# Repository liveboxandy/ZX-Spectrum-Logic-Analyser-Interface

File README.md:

# ZX-Spectrum-Logic-Analyser-Interface
Copied and Modified from an original idea (V3.1) by HappyLittleDiodes(Jim)

Increased space between Logic Analyser Connectors so as to allow for Pico on 10mm headers on Logic Analyser PCB's

PCB size increased to allow for the above

Added 3 pin header to allow for manual connection to the unused channels (6,7 and 26)

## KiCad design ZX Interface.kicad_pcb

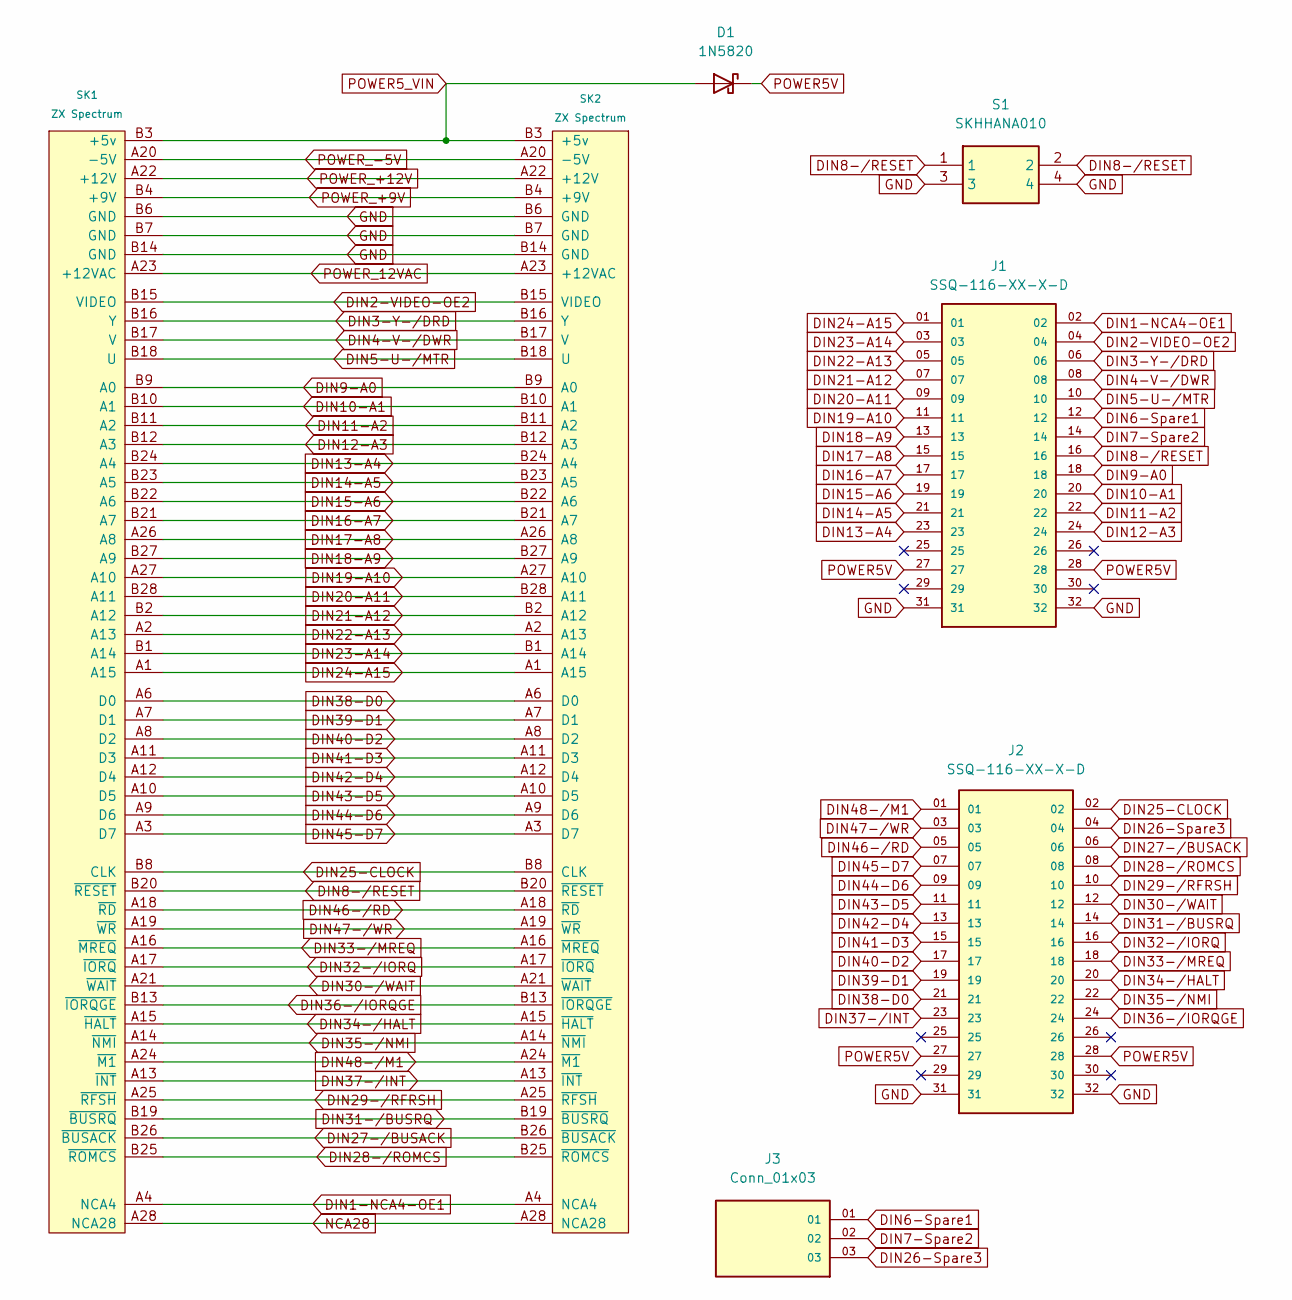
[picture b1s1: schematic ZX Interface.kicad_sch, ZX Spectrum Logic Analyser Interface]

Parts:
D1: 1N5820; D_DO-201AD_P15.24mm_Horizontal
J1, J2: SSQ-116-XX-X-D; SAMTEC_SSQ-116-XX-X-D; PARTREV A
J3: Conn_01x03; SAMTEC_TSW-103-07-G-S; PARTREV R
S1: SKHHANA010; Mouser Part Number 688-SKHHAN
SK1, SK2: ZX Spectrum; ZX_Spectrum_BUS_Edge_Connector Horizontal

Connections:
DIN1-NCA4-OE1: J1.02, SK1.A4 (NCA4), SK2.A4 (NCA4)
DIN2-VIDEO-OE2: J1.04, SK1.B15 (VIDEO), SK2.B15 (VIDEO)
DIN3-Y-/DRD: J1.06, SK1.B16 (Y), SK2.B16 (Y)
DIN4-V-/DWR: J1.08, SK1.B17 (V), SK2.B17 (V)
DIN5-U-/MTR: J1.10, SK1.B18 (U), SK2.B18 (U)
DIN6-Spare1: J1.12, J3.01
DIN7-Spare2: J1.14, J3.02
DIN8-/RESET: J1.16, S1.1, S1.2, SK1.B20 (~RESET), SK2.B20 (~RESET)
DIN9-A0: J1.18, SK1.B9 (A0), SK2.B9 (A0)
DIN10-A1: J1.20, SK1.B10 (A1), SK2.B10 (A1)
DIN11-A2: J1.22, SK1.B11 (A2), SK2.B11 (A2)
DIN12-A3: J1.24, SK1.B12 (A3), SK2.B12 (A3)
DIN13-A4: J1.23, SK1.B24 (A4), SK2.B24 (A4)
DIN14-A5: J1.21, SK1.B23 (A5), SK2.B23 (A5)
DIN15-A6: J1.19, SK1.B22 (A6), SK2.B22 (A6)
DIN16-A7: J1.17, SK1.B21 (A7), SK2.B21 (A7)
DIN17-A8: J1.15, SK1.A26 (A8), SK2.A26 (A8)
DIN18-A9: J1.13, SK1.B27 (A9), SK2.B27 (A9)
DIN19-A10: J1.11, SK1.A27 (A10), SK2.A27 (A10)
DIN20-A11: J1.09, SK1.B28 (A11), SK2.B28 (A11)
DIN21-A12: J1.07, SK1.B2 (A12), SK2.B2 (A12)
DIN22-A13: J1.05, SK1.A2 (A13), SK2.A2 (A13)
DIN23-A14: J1.03, SK1.B1 (A14), SK2.B1 (A14)
DIN24-A15: J1.01, SK1.A1 (A15), SK2.A1 (A15)
DIN25-CLOCK: J2.02, SK1.B8 (CLK), SK2.B8 (CLK)
DIN26-Spare3: J2.04, J3.03
DIN27-/BUSACK: J2.06, SK1.B26 (~BUSACK), SK2.B26 (~BUSACK)
DIN28-/ROMCS: J2.08, SK1.B25 (~ROMCS), SK2.B25 (~ROMCS)
DIN29-/RFRSH: J2.10, SK1.A25 (~RFSH), SK2.A25 (~RFSH)
DIN30-/WAIT: J2.12, SK1.A21 (~WAIT), SK2.A21 (~WAIT)
DIN31-/BUSRQ: J2.14, SK1.B19 (~BUSRQ), SK2.B19 (~BUSRQ)
DIN32-/IORQ: J2.16, SK1.A17 (~IORQ), SK2.A17 (~IORQ)
DIN33-/MREQ: J2.18, SK1.A16 (~MREQ), SK2.A16 (~MREQ)
DIN34-/HALT: J2.20, SK1.A15 (~HALT), SK2.A15 (~HALT)
DIN35-/NMI: J2.22, SK1.A14 (~NMI), SK2.A14 (~NMI)
DIN36-/IORQGE: J2.24, SK1.B13 (~IORQGE), SK2.B13 (~IORQGE)
DIN37-/INT: J2.23, SK1.A13 (~INT), SK2.A13 (~INT)
DIN38-D0: J2.21, SK1.A6 (D0), SK2.A6 (D0)
DIN39-D1: J2.19, SK1.A7 (D1), SK2.A7 (D1)
DIN40-D2: J2.17, SK1.A8 (D2), SK2.A8 (D2)
DIN41-D3: J2.15, SK1.A11 (D3), SK2.A11 (D3)
DIN42-D4: J2.13, SK1.A12 (D4), SK2.A12 (D4)
DIN43-D5: J2.11, SK1.A10 (D5), SK2.A10 (D5)
DIN44-D6: J2.09, SK1.A9 (D6), SK2.A9 (D6)
DIN45-D7: J2.07, SK1.A3 (D7), SK2.A3 (D7)
DIN46-/RD: J2.05, SK1.A18 (~RD), SK2.A18 (~RD)
DIN47-/WR: J2.03, SK1.A19 (~WR), SK2.A19 (~WR)
DIN48-/M1: J2.01, SK1.A24 (~M1), SK2.A24 (~M1)
GND: J1.31, J1.32, J2.31, J2.32, S1.3, S1.4, SK1.B6 (GND), SK1.B7 (GND), SK1.B14 (GND), SK2.B6 (GND), SK2.B7 (GND), SK2.B14 (GND)
NCA28: SK1.A28 (NCA28), SK2.A28 (NCA28)
POWER5V: D1.1 (K), J1.27, J1.28, J2.27, J2.28
POWER5_VIN: D1.2 (A), SK1.B3 (+5v), SK2.B3 (+5v)
POWER_12VAC: SK1.A23 (+12VAC), SK2.A23 (+12VAC)
POWER_+9V: SK1.B4 (+9V), SK2.B4 (+9V)
POWER_+12V: SK1.A22 (+12V), SK2.A22 (+12V)
POWER_-5V: SK1.A20 (-5V), SK2.A20 (-5V)

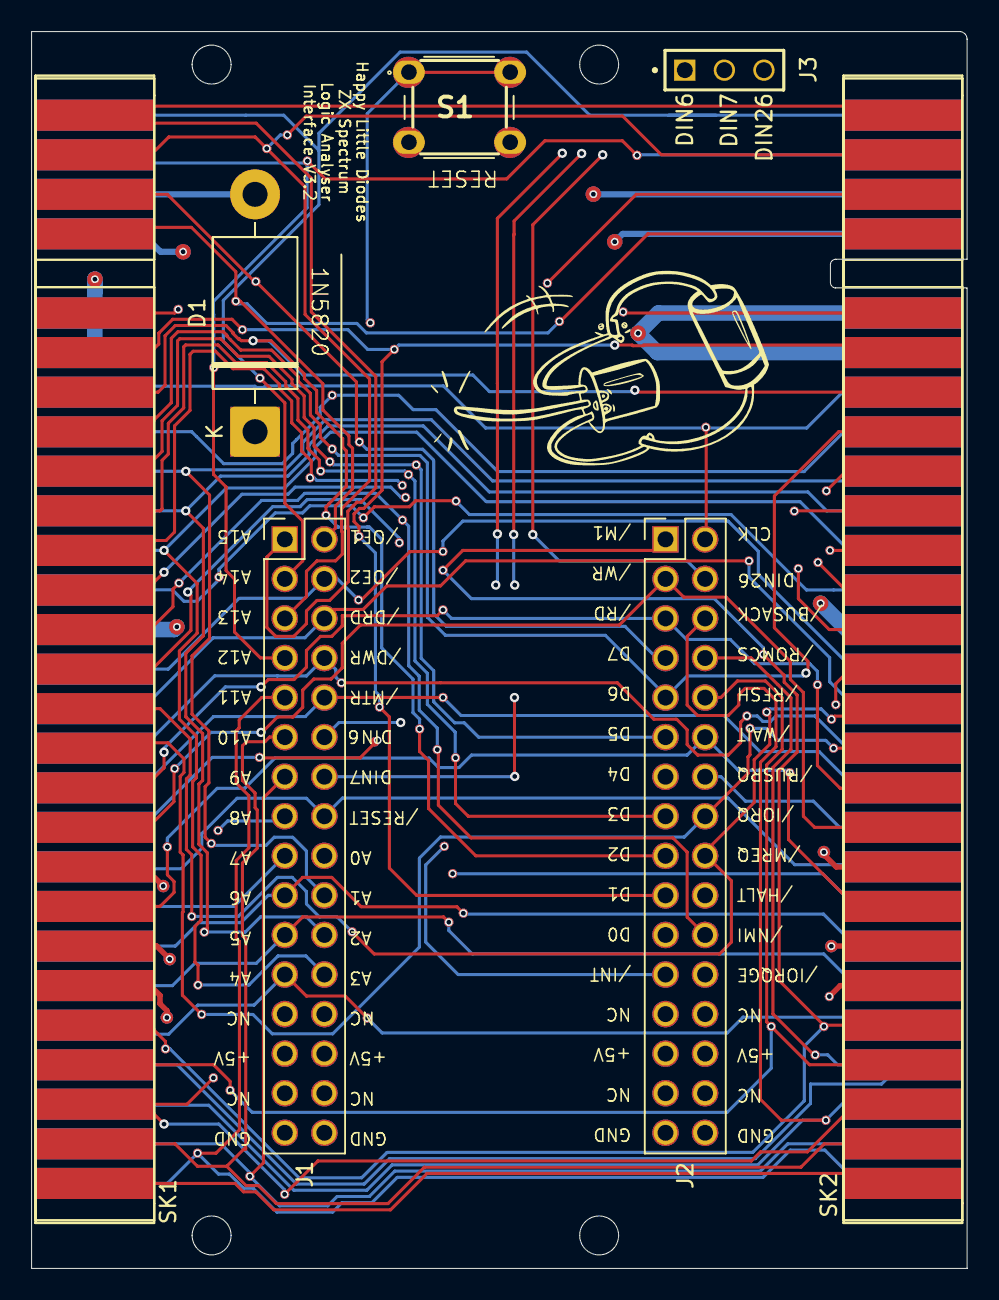
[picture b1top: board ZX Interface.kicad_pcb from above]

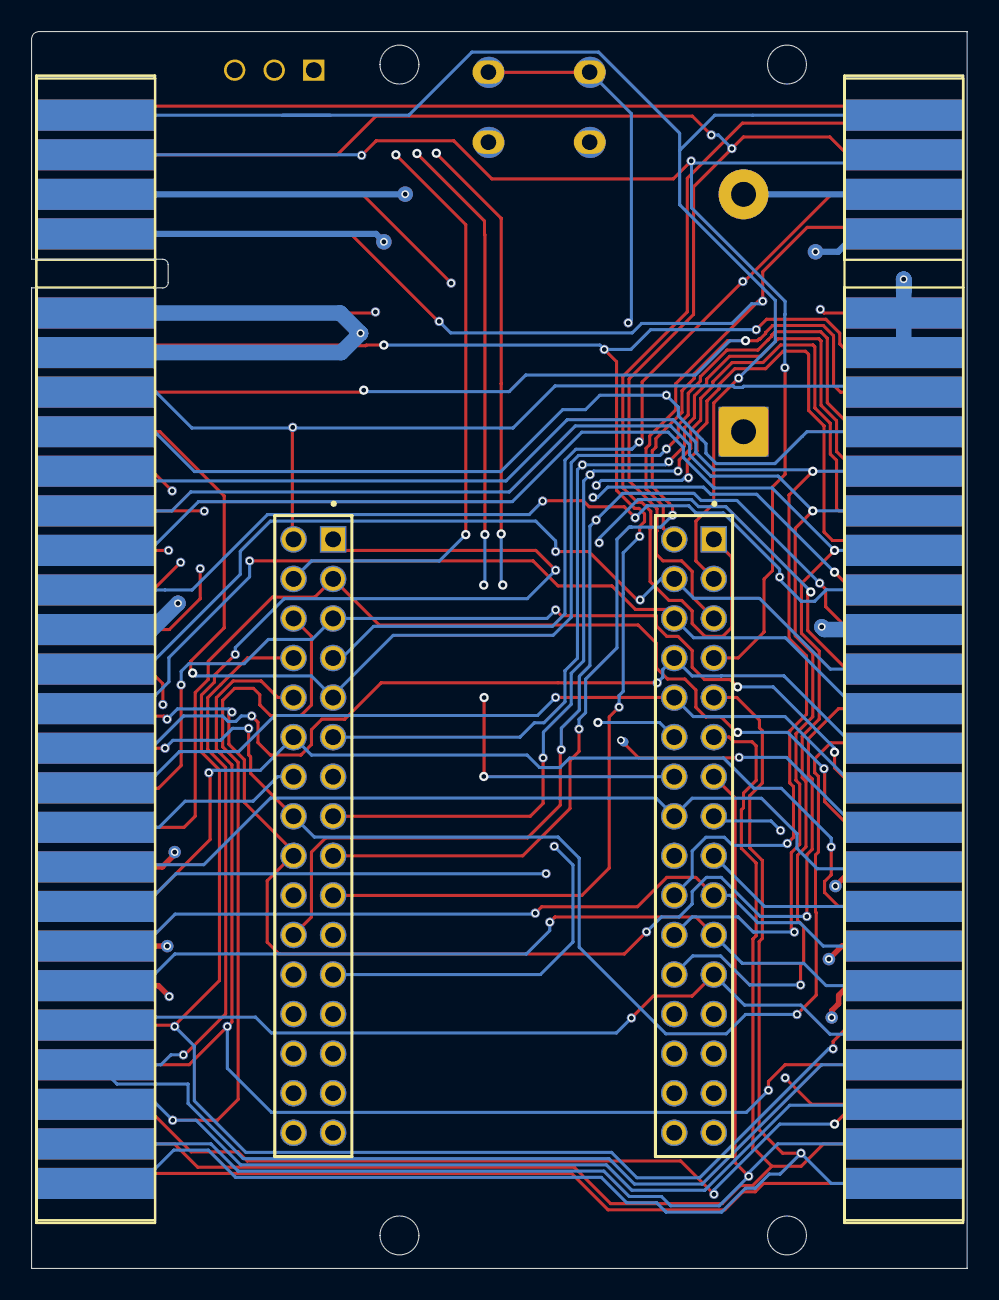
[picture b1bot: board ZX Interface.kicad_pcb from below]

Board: 4 copper layers, 60.1 x 79.4 mm, 7 parts (2 on the bottom side), 56 nets.

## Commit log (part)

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2026-01-22 Revise README with project updates and modifications
    Updated project description and added details about modifications.
